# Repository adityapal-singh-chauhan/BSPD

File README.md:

<H1>BSPD - Brake System Plausibiltiy Device</H1>  
<BR /><H3>
A non - programmable brake, accelerator plausibility circuit.<BR />
Built for FSAE, according to Formula Bharat specs 2024.<BR /></H3>
<ul>
	<li>It feautes upper and lower thresholds for fault detection</li>
	<li>Disconnection or damage to sensor will also trigger the circuit.</li>
  <li>acc/brake_upper_trig - potentiometer sets the sensors output voltage trigger threshold.</li>
  <li>acc/brake_lower_trig - potentiometer sets the minimum volatage output of the sensor.</li>
  <li>The timing for 500ms wait and 10s shutdown can also be fine tuned.</li> 
	<li>onboard volatge regulation(input 15v - 5.5v)</li>
</ul>

SCHEMATIC

PCB layout

LTspice sim:

red - fault signal<BR />
green - 500ms wait<BR />
blue - shutdown trigger<BR />

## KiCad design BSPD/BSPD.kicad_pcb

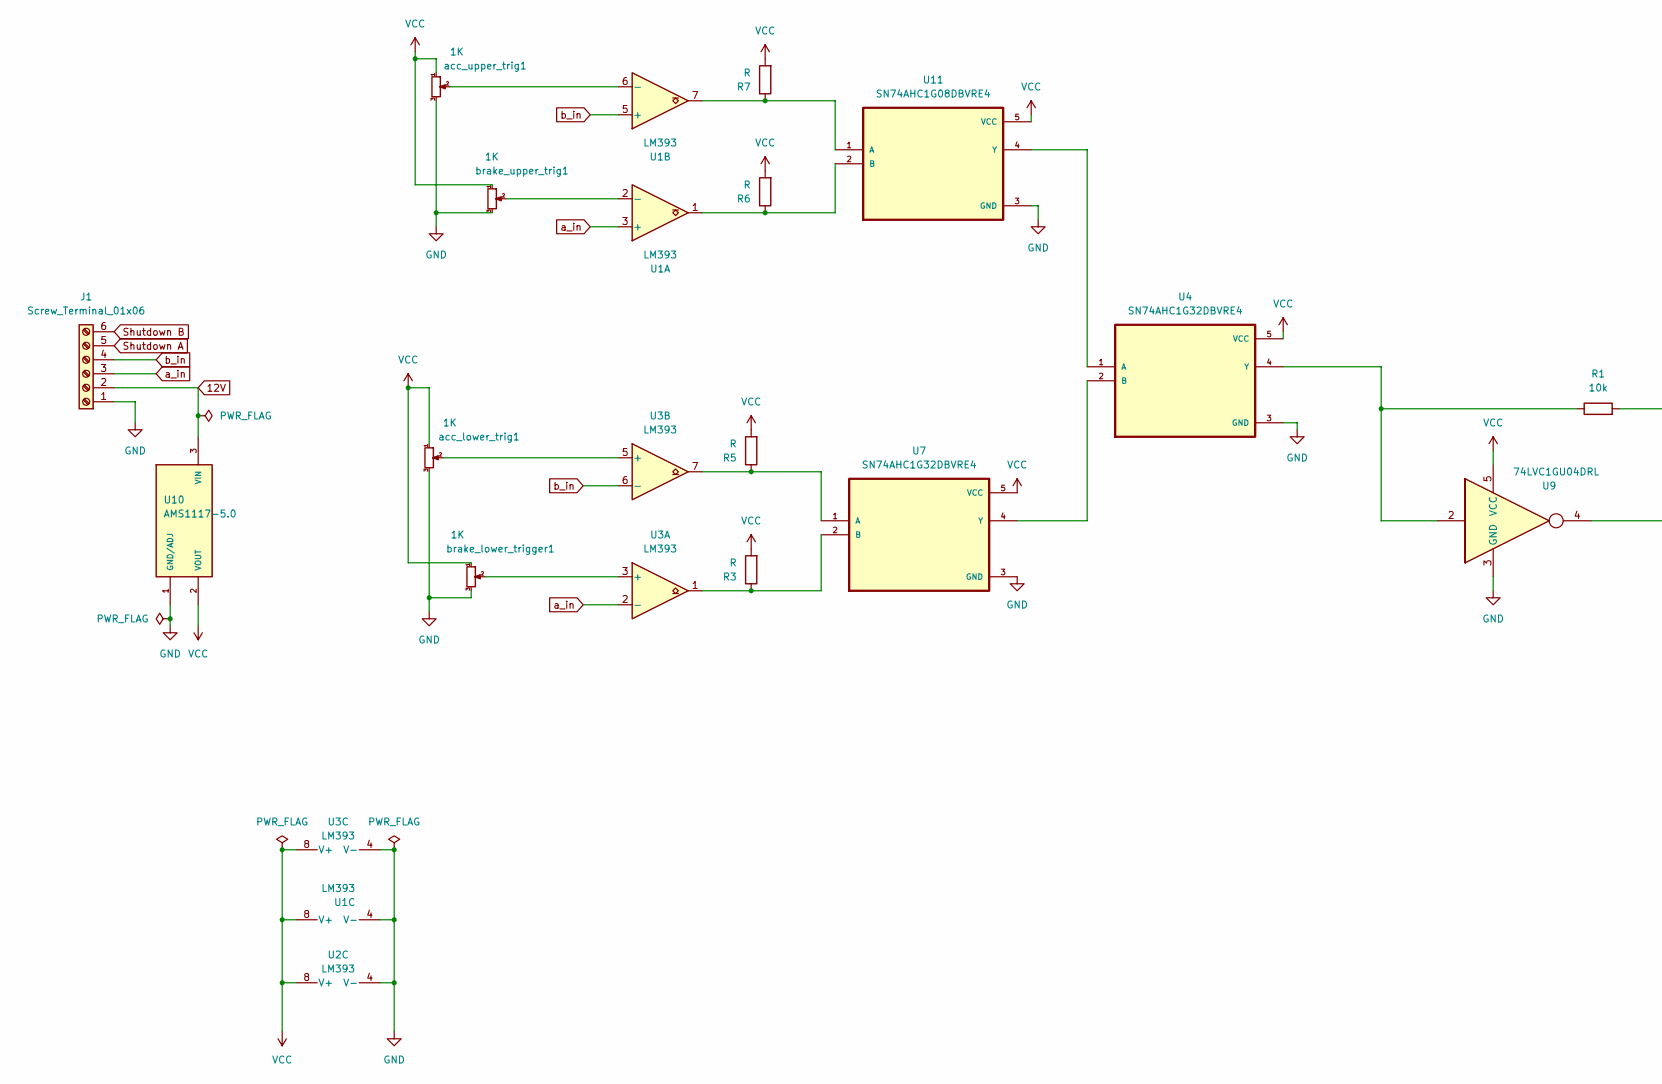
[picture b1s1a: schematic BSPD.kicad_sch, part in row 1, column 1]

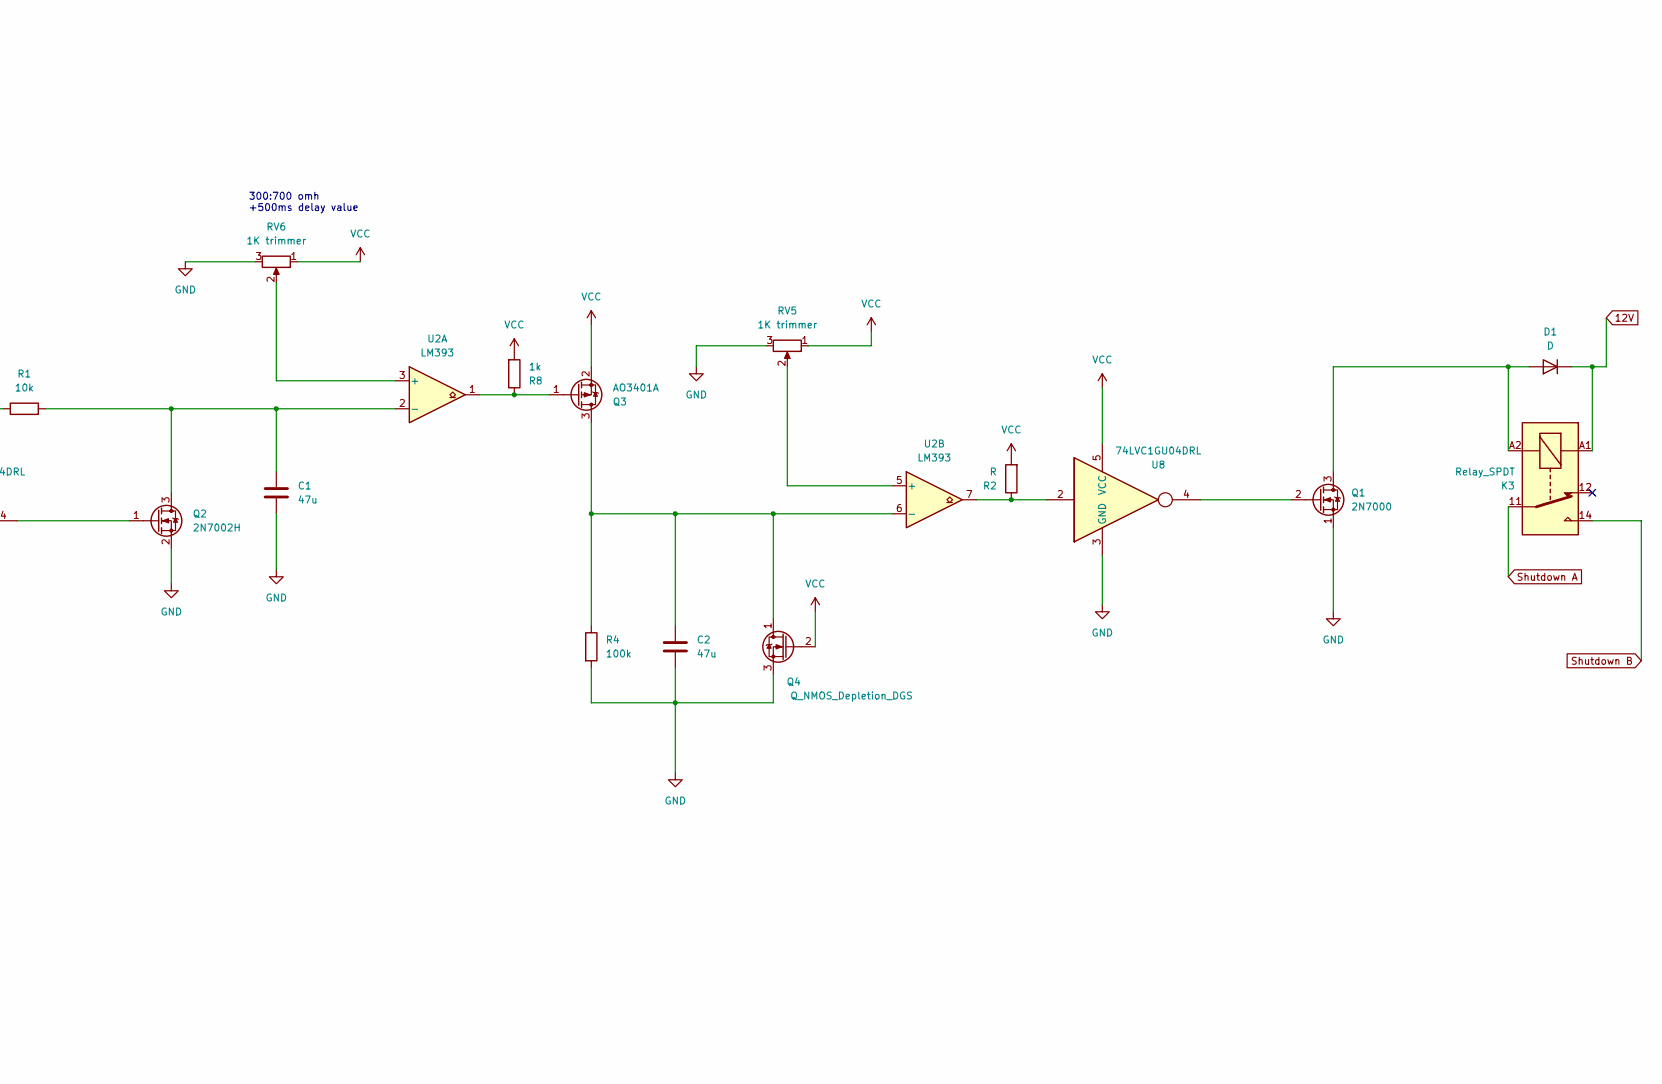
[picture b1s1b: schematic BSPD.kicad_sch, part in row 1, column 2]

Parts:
C1, C2: 47u; C_Elec_6.3x7.7
D1: D; D_1206_3216Metric_Pad1.42x1.75mm_HandSolder
J1: Screw_Terminal_01x06; TerminalBlock_bornier-6_P5.08mm
K3: Relay_SPDT; Relay_SPDT_Finder_36.11
Q1: 2N7000; SOT-23
Q2: 2N7002H; SOT-23
Q3: AO3401A; SOT-23
Q4: Q_NMOS_Depletion_DGS; SOT-23
R1: 10k; R_1206_3216Metric
R2, R3, R5, R6, R7: R; R_1206_3216Metric
R4: 100k; R_1206_3216Metric
R8: 1k; R_1206_3216Metric
RV5, RV6: 1K trimmer; Potentiometer_Bourns_3296W_Vertical
U1, U2, U3: LM393; SOIC-8-1EP_3.9x4.9mm_P1.27mm_EP2.29x3mm
U4, U7: SN74AHC1G32DBVRE4; SOT-23-5
U8, U9: 74LVC1GU04DRL; SOT-23-5
U10: AMS1117-5.0; SOT-223; PARTREV N/A
U11: SN74AHC1G08DBVRE4; SOT-23-5
acc_lower_trig1: 1K; Potentiometer_Bourns_3296W_Vertical
acc_upper_trig1: 1K; Potentiometer_Bourns_3296W_Vertical
brake_lower_trigger1: 1K; Potentiometer_Bourns_3296W_Vertical
brake_upper_trig1: 1K; Potentiometer_Bourns_3296W_Vertical

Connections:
12V: D1.1 (K), J1.2, K3.A1, U10.3 (VIN)
GND: C1.2, C2.2, J1.1, Q1.1 (S), Q2.2 (S), Q4.3 (S), R4.2, RV5.3, RV6.3, U1.4 (V-), U2.4 (V-), U3.4 (V-), U4.3 (GND), U7.3 (GND), U8.3 (GND), U9.3 (GND), U10.1 (GND/ADJ), U11.3 (GND), acc_lower_trig1.3, acc_upper_trig1.3, brake_lower_trigger1.3, brake_upper_trig1.3; also elsewhere on the board
unnamed: D1.2 (A), K3.A2, Q1.3 (D)
unnamed: Q1.2 (G), U8.4
unnamed: C1.1, Q2.3 (D), R1.2, U2.2 (-)
unnamed: Q2.1 (G), U9.4
unnamed: C2.1, Q3.3 (D), Q4.1 (D), R4.1, U2.6 (-)
unnamed: Q3.1 (G), R8.1, U2.1
unnamed: R2.1, U2.7, U8.2
unnamed: U1.2 (-), brake_upper_trig1.2
unnamed: U1.6 (-), acc_upper_trig1.2
unnamed: RV6.2, U2.3 (+)
unnamed: RV5.2, U2.5 (+)
unnamed 13: U3.3 (+), brake_lower_trigger1.2; also elsewhere on the board
unnamed: U3.5 (+), acc_lower_trig1.2
unnamed: U4.2 (B), U7.4 (Y)
unnamed: R1.1, U4.4 (Y), U9.2
unnamed: R5.1, U3.7, U7.1 (A)
unnamed: R3.1, U3.1, U7.2 (B)
unnamed: R7.1, U1.7, U11.1 (A)
unnamed: R6.1, U1.1, U11.2 (B)
unnamed: U4.1 (A), U11.4 (Y)
Shutdown A: J1.5, K3.11
Shutdown B: J1.6, K3.14
VCC: Q3.2 (S), Q4.2 (G), R2.2, R3.2, R5.2, R6.2, R7.2, R8.2, RV5.1, RV6.1, U1.8 (V+), U2.8 (V+), U3.8 (V+), U4.5 (VCC), U7.5 (VCC), U8.5 (VCC), U9.5 (VCC), U10.2 (VOUT), U11.5 (VCC), acc_lower_trig1.1, acc_upper_trig1.1, brake_lower_trigger1.1, brake_upper_trig1.1; also elsewhere on the board
a_in: J1.3, U1.3 (+), U3.2 (-)
b_in: J1.4, U1.5 (+), U3.6 (-)

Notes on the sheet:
300:700 omh +500ms delay value

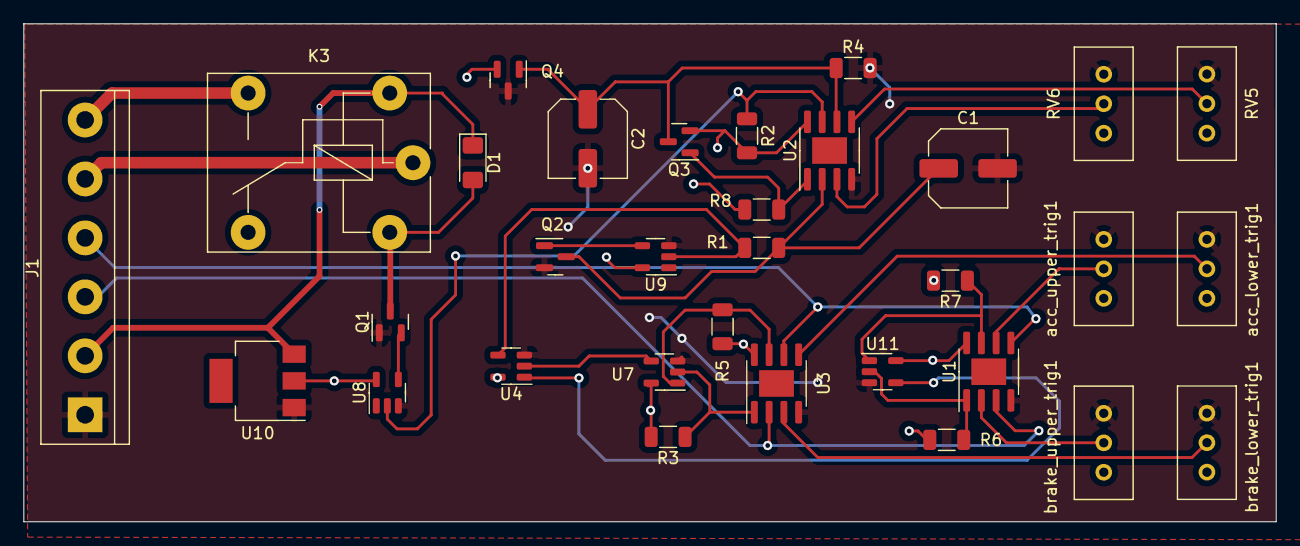
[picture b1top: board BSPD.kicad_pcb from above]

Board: 2 copper layers, 107.9 x 42.9 mm, 32 parts (0 on the bottom side), 27 nets.

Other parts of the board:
brake_lower_trig1: 1K; Potentiometer_Bourns_3296W_Vertical

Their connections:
GND: brake_lower_trig1.3; also elsewhere on the board
unnamed 13: brake_lower_trig1.2; also elsewhere on the board
VCC: brake_lower_trig1.1; also elsewhere on the board
